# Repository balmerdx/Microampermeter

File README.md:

# Микроамперметр

Микроамперметр перфекциониста, с возможностью посмотреть график и гистограмму получаемого тока.
Предназначен для того, что-бы отлаживать низкопотребляющие железки,
которые во сне потребляют микроамперы, а когда проснулись, то могут потреблять десятки миллиампер.

* [Видео с возможностями прибора.](https://www.youtube.com/watch?v=IdX-KkagfNQ)

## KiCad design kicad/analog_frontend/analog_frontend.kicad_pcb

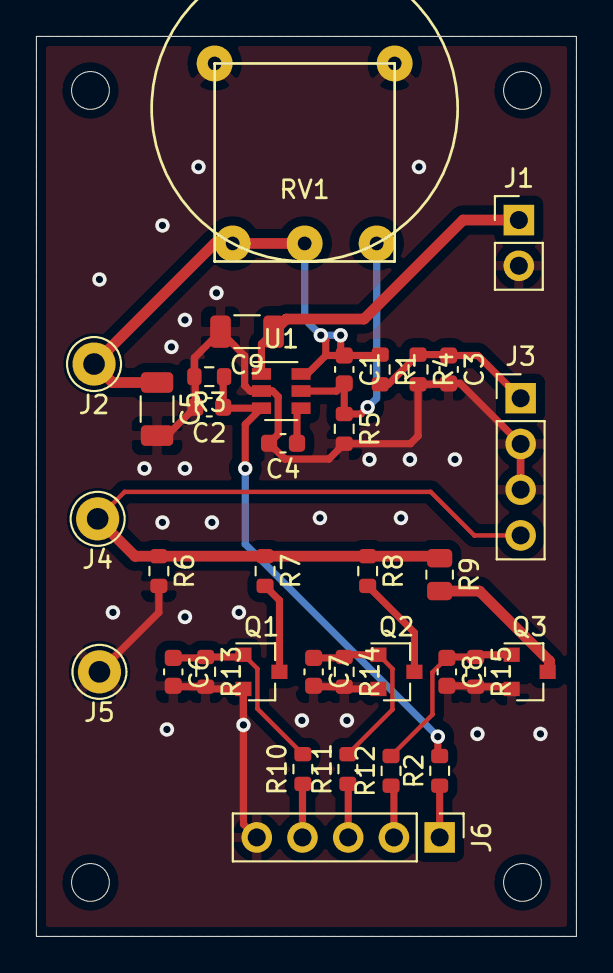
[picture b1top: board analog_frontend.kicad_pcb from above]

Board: 2 copper layers, 30.0 x 50.0 mm, 35 parts (0 on the bottom side), 18 nets.

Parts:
C1: 22; C_0603_1608Metric
C2, C6, C7, C8: 22n; C_0603_1608Metric
C3: 1n; C_0603_1608Metric
C4: 10n; C_0603_1608Metric
C5: 25u; C_1206_3216Metric
C9: 10u; C_1206_3216Metric
J1: Power; PinHeader_1x02_P2.54mm_Vertical
J2: Vout; Pin_D1.0mm_L10.0mm_LooseFit
J3: ADC; PinHeader_1x04_P2.54mm_Vertical
J4: Isense; Pin_D1.0mm_L10.0mm_LooseFit
J5: GND; Pin_D1.0mm_L10.0mm_LooseFit
J6: Digital; PinHeader_1x05_P2.54mm_Vertical
Q1, Q2: SI2302; SOT-23
Q3: IRLML2502; SOT-23
R1, R4: 2k; R_0603_1608Metric
R2, R5: 10k; R_0603_1608Metric
R3: 330k; R_0603_1608Metric
R6: 1k; R_0603_1608Metric
R7: 100; R_0603_1608Metric
R8: 10; R_0603_1608Metric
R9: 1; R_0805_2012Metric
R10, R11, R12: 4.7k; R_0603_1608Metric
R13, R14, R15: 68k; R_0603_1608Metric
RV1: 20k; Potentiometer_10mm
U1: TPS79301-EP; SOT-23-6

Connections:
+BATT: C9.1, J1.1, U1.1
/Vout: C1.1, C5.1, J2.1, R1.1, RV1.1, RV1.2, U1.6
EN_V: J6.1, R2.1
GND: C2.2, C3.2, C4.2, C5.2, C6.2, C7.2, C8.2, C9.2, J1.2, J3.2, J3.3, J5.1, J6.5, Q1.2, Q2.2, Q3.2, R3.2, R4.2, R5.2, R6.2, R13.2, R14.2, R15.2, RV1.4, RV1.5, U1.2
I_ADC: J3.4, J4.1, R6.1, R7.1, R8.1, R9.1
unnamed: C1.2, R5.1, RV1.3, U1.5
unnamed: C2.1, R2.2, R3.1, U1.3
unnamed: C4.1, U1.4
unnamed: C6.1, Q1.1, R10.2, R13.1
unnamed: C7.1, Q2.1, R11.2, R14.1
unnamed: C8.1, Q3.1, R12.2, R15.1
unnamed: Q1.3, R7.2
unnamed: Q2.3, R8.2
unnamed: Q3.3, R9.2
ON_1: J6.2, R12.1
ON_10: J6.3, R11.1
ON_100: J6.4, R10.1
V_ADC: C3.1, J3.1, R1.2, R4.1

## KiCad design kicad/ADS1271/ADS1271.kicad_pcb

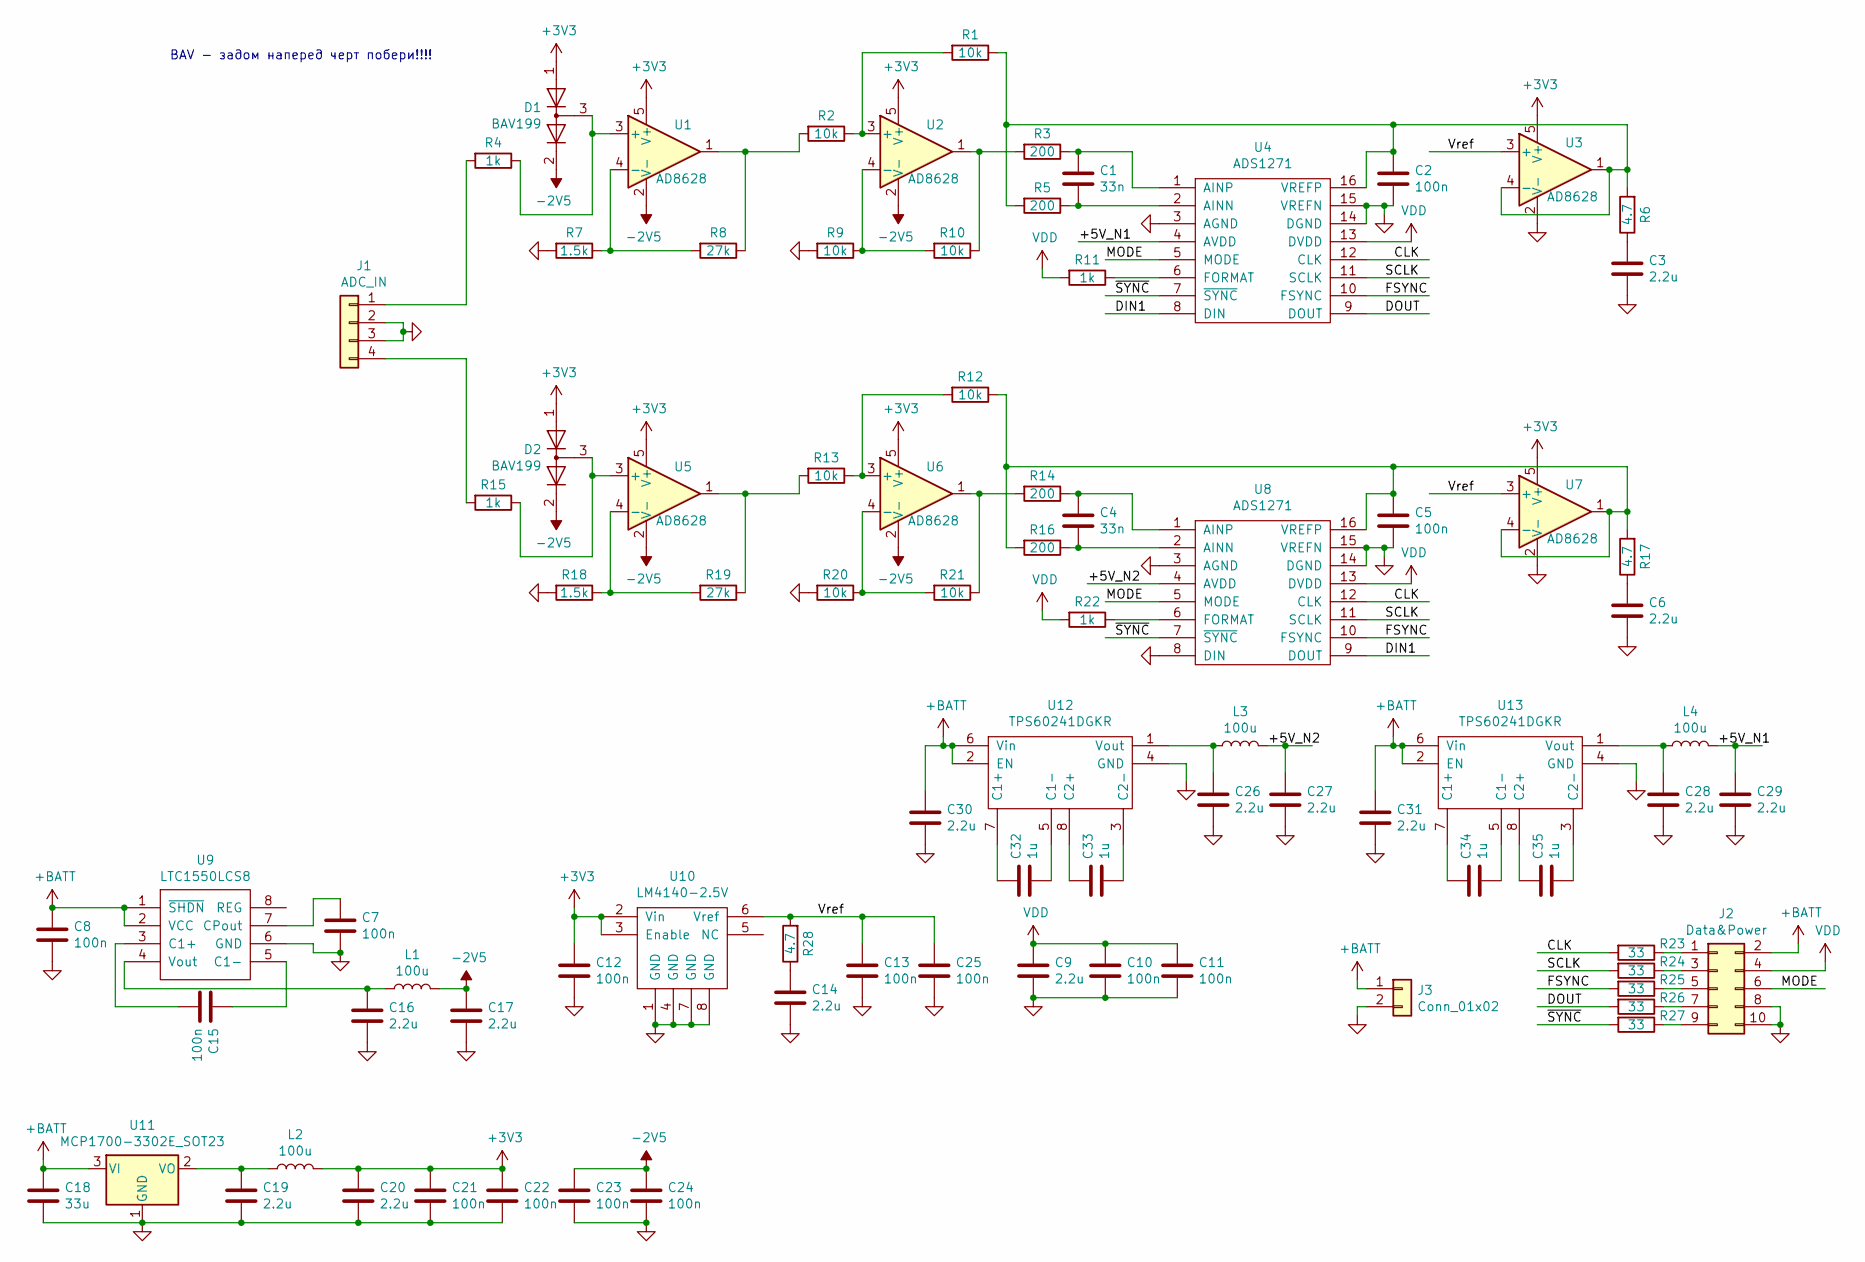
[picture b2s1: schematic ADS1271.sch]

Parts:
C1, C4: 33n; C_Disc_D7.5mm_W2.5mm_P5.00mm
C2, C5, C7, C8, C10, C11, C12, C13, C15, C21, C22, C23, C24, C25: 100n; C_0603_1608Metric
C3, C6, C9, C14, C16, C17, C19, C20, C26, C27, C28, C29, C30, C31: 2.2u; C_0805_2012Metric
C18: 33u; C_1206_3216Metric
C32, C33, C34, C35: 1u; C_0603_1608Metric
D1, D2: BAV199; SOT-23
J1: ADC_IN; PinHeader_1x04_P2.54mm_Vertical
J2: Data&Power; PinHeader_2x05_P2.54mm_Horizontal
J3: Conn_01x02; PinHeader_1x02_P2.54mm_Vertical
L1, L2, L3, L4: 100u; L_Axial_L9.5mm_D4.0mm_P12.70mm_Horizontal_Fastron_SMCC
R1, R2, R9, R10, R12, R13, R20, R21: 10k; R_0603_1608Metric
R3, R5, R14, R16: 200; R_0603_1608Metric
R4, R11, R15, R22: 1k; R_0603_1608Metric
R6, R17, R28: 4.7; R_0603_1608Metric
R7, R18: 1.5k; R_0603_1608Metric
R8, R19: 27k; R_0603_1608Metric
R23, R24, R25, R26, R27: 33; R_0603_1608Metric
U1, U2, U3, U5, U6, U7: AD8628; SOT-23-5
U4, U8: ADS1271; TSSOP-16_4.4x5mm_P0.65mm
U9: LTC1550LCS8; TSSOP-8_3x3mm_P0.65mm
U10: LM4140-2.5V; SO-8_3.9x4.9mm_P1.27mm
U11: MCP1700-3302E_SOT23; SOT-23
U12, U13: TPS60241DGKR; TSSOP-8_3x3mm_P0.65mm

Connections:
+3V3: C12.1, C20.1, C21.1, C22.1, D1.1 (K), D2.1 (K), L2.2, U1.5 (V+), U2.5 (V+), U3.5 (V+), U5.5 (V+), U6.5 (V+), U7.5 (V+), U10.2 (Vin), U10.3 (Enable)
+BATT: C8.1, C18.1, C30.1, C31.1, J2.2, J3.1, U9.1 (~SHDN), U9.2 (VCC), U11.3 (VI), U12.2 (EN), U12.6 (Vin), U13.2 (EN), U13.6 (Vin)
-2V5: C17.1, C23.1, C24.1, D1.2 (A), D2.2 (A), L1.2, U1.2 (V-), U2.2 (V-), U5.2 (V-), U6.2 (V-)
/+5V_N1: C29.1, L4.2, U4.4 (AVDD)
/+5V_N2: C27.1, L3.2, U8.4 (AVDD)
/CLK: R23.2, U4.12 (CLK), U8.12 (CLK)
/DIN1: U4.8 (DIN), U8.9 (DOUT)
/DOUT: R26.2, U4.9 (DOUT)
/FSYNC: R25.2, U4.10 (FSYNC), U8.10 (FSYNC)
/MODE: J2.6, U4.5 (MODE), U8.5 (MODE)
/SCLK: R24.2, U4.11 (SCLK), U8.11 (SCLK)
/Vref: C13.1, C25.1, R28.2, U3.3 (+), U7.3 (+), U10.6 (Vref)
/~SYNC: R27.2, U4.7 (~SYNC), U8.7 (~SYNC)
GND: C2.2, C3.2, C5.2, C6.2, C7.2, C8.2, C9.2, C10.2, C11.2, C12.2, C13.2, C14.2, C16.2, C17.2, C18.2, C19.2, C20.2, C21.2, C22.2, C23.2, C24.2, C25.2, C26.2, C27.2, C28.2, C29.2, C30.2, C31.2, J1.2, J1.3, J2.8, J2.10, J3.2, R7.2, R9.2, R18.2, R20.2, U3.2 (V-), U4.3 (AGND), U4.14 (DGND), U4.15 (VREFN), U7.2 (V-), U8.3 (AGND), U8.8 (DIN), U8.14 (DGND), U8.15 (VREFN), U9.6 (GND), U10.1 (GND), U10.4 (GND), U10.7 (GND), U10.8 (GND), U11.1 (GND), U12.4 (GND), U13.4 (GND)
unnamed: C1.1, R3.1, U4.1 (AINP)
unnamed: C1.2, R5.1, U4.2 (AINN)
unnamed: C2.1, R1.1, R5.2, R6.2, U3.1, U3.4 (-), U4.16 (VREFP)
unnamed: C3.1, R6.1
unnamed: C4.1, R14.1, U8.1 (AINP)
unnamed: C4.2, R16.1, U8.2 (AINN)
unnamed: C5.1, R12.1, R16.2, R17.2, U7.1, U7.4 (-), U8.16 (VREFP)
unnamed: C6.1, R17.1
unnamed: C7.1, U9.7 (CPout)
unnamed: C14.1, R28.1
unnamed: C15.1, U9.5 (C1-)
unnamed: C15.2, U9.3 (C1+)
unnamed: C16.1, L1.1, U9.4 (Vout)
unnamed: C19.1, L2.1, U11.2 (VO)
unnamed: C26.1, L3.1, U12.1 (Vout)
unnamed: C28.1, L4.1, U13.1 (Vout)
unnamed: C32.1, U12.7 (C1+)
unnamed: C32.2, U12.5 (C1-)
unnamed: C33.1, U12.8 (C2+)
unnamed: C33.2, U12.3 (C2-)
unnamed: C34.1, U13.7 (C1+)
unnamed: C34.2, U13.5 (C1-)
unnamed: C35.1, U13.8 (C2+)
unnamed: C35.2, U13.3 (C2-)
unnamed: D1.3 (K), R4.1, U1.3 (+)
unnamed: D2.3 (K), R15.1, U5.3 (+)
unnamed: J1.1, R4.2
unnamed: J1.4, R15.2
unnamed: J2.1, R23.1
unnamed: J2.3, R24.1
unnamed: J2.5, R25.1
unnamed: J2.7, R26.1
unnamed: J2.9, R27.1
unnamed: R1.2, R2.1, U2.3 (+)
unnamed: R2.2, R8.1, U1.1
unnamed: R7.1, R8.2, U1.4 (-)
unnamed: R3.2, R10.1, U2.1
unnamed: R9.1, R10.2, U2.4 (-)
unnamed: R11.1, U4.6 (FORMAT)
unnamed: R12.2, R13.1, U6.3 (+)
unnamed: R13.2, R19.1, U5.1
unnamed: R14.2, R21.1, U6.1
unnamed: R18.1, R19.2, U5.4 (-)
unnamed: R20.1, R21.2, U6.4 (-)
unnamed: R22.1, U8.6 (FORMAT)
VDD: C9.1, C10.1, C11.1, J2.4, R11.2, R22.2, U4.13 (DVDD), U8.13 (DVDD)

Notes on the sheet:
BAV - задом наперед черт побери!!!!

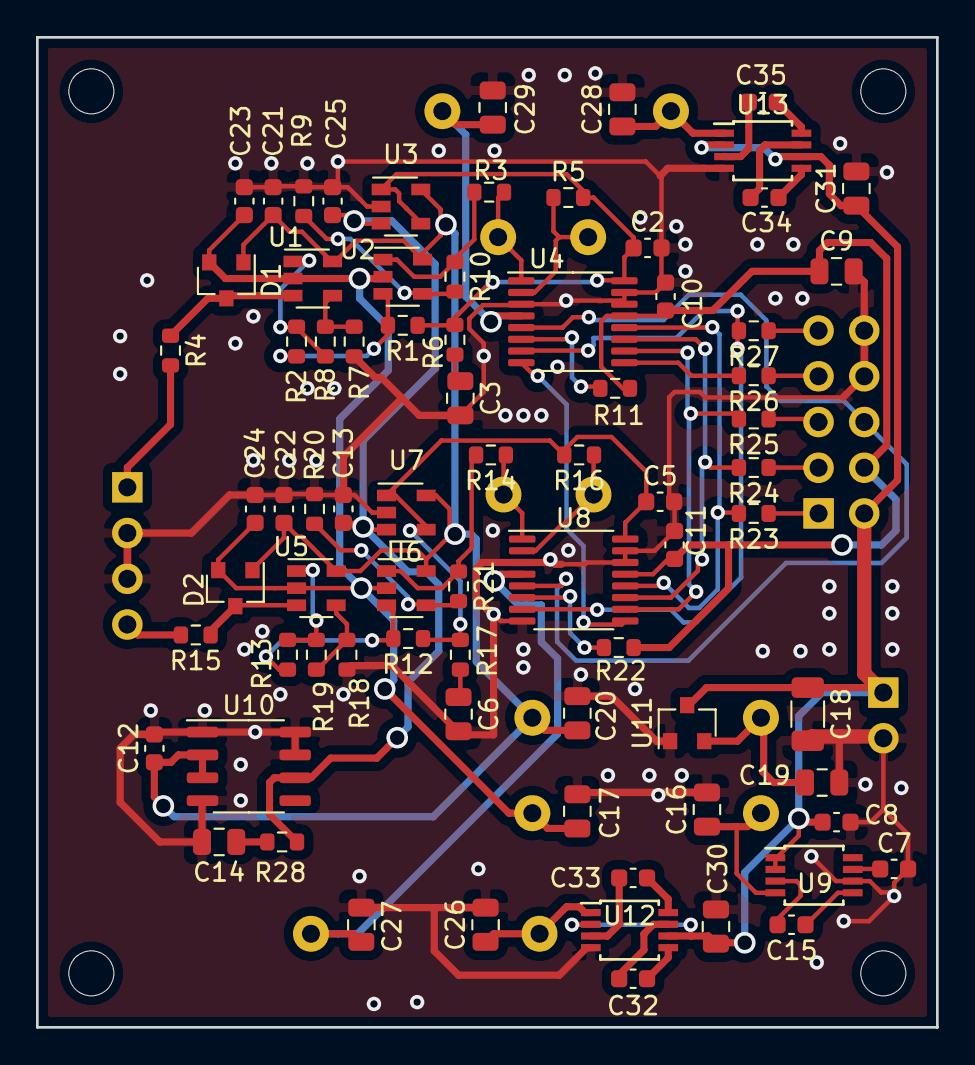
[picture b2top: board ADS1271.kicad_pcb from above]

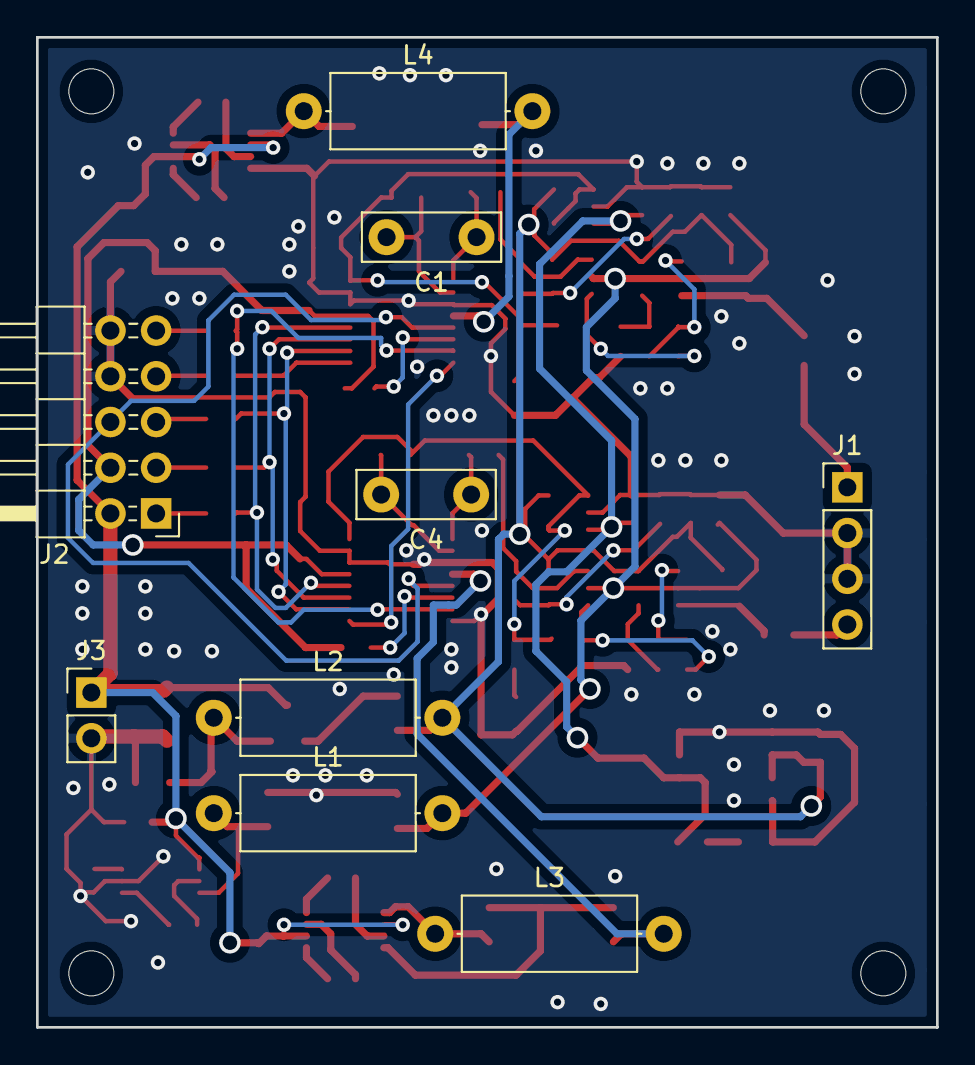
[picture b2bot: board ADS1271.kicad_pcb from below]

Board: 2 copper layers, 50.0 x 55.0 mm, 85 parts (9 on the bottom side), 60 nets.

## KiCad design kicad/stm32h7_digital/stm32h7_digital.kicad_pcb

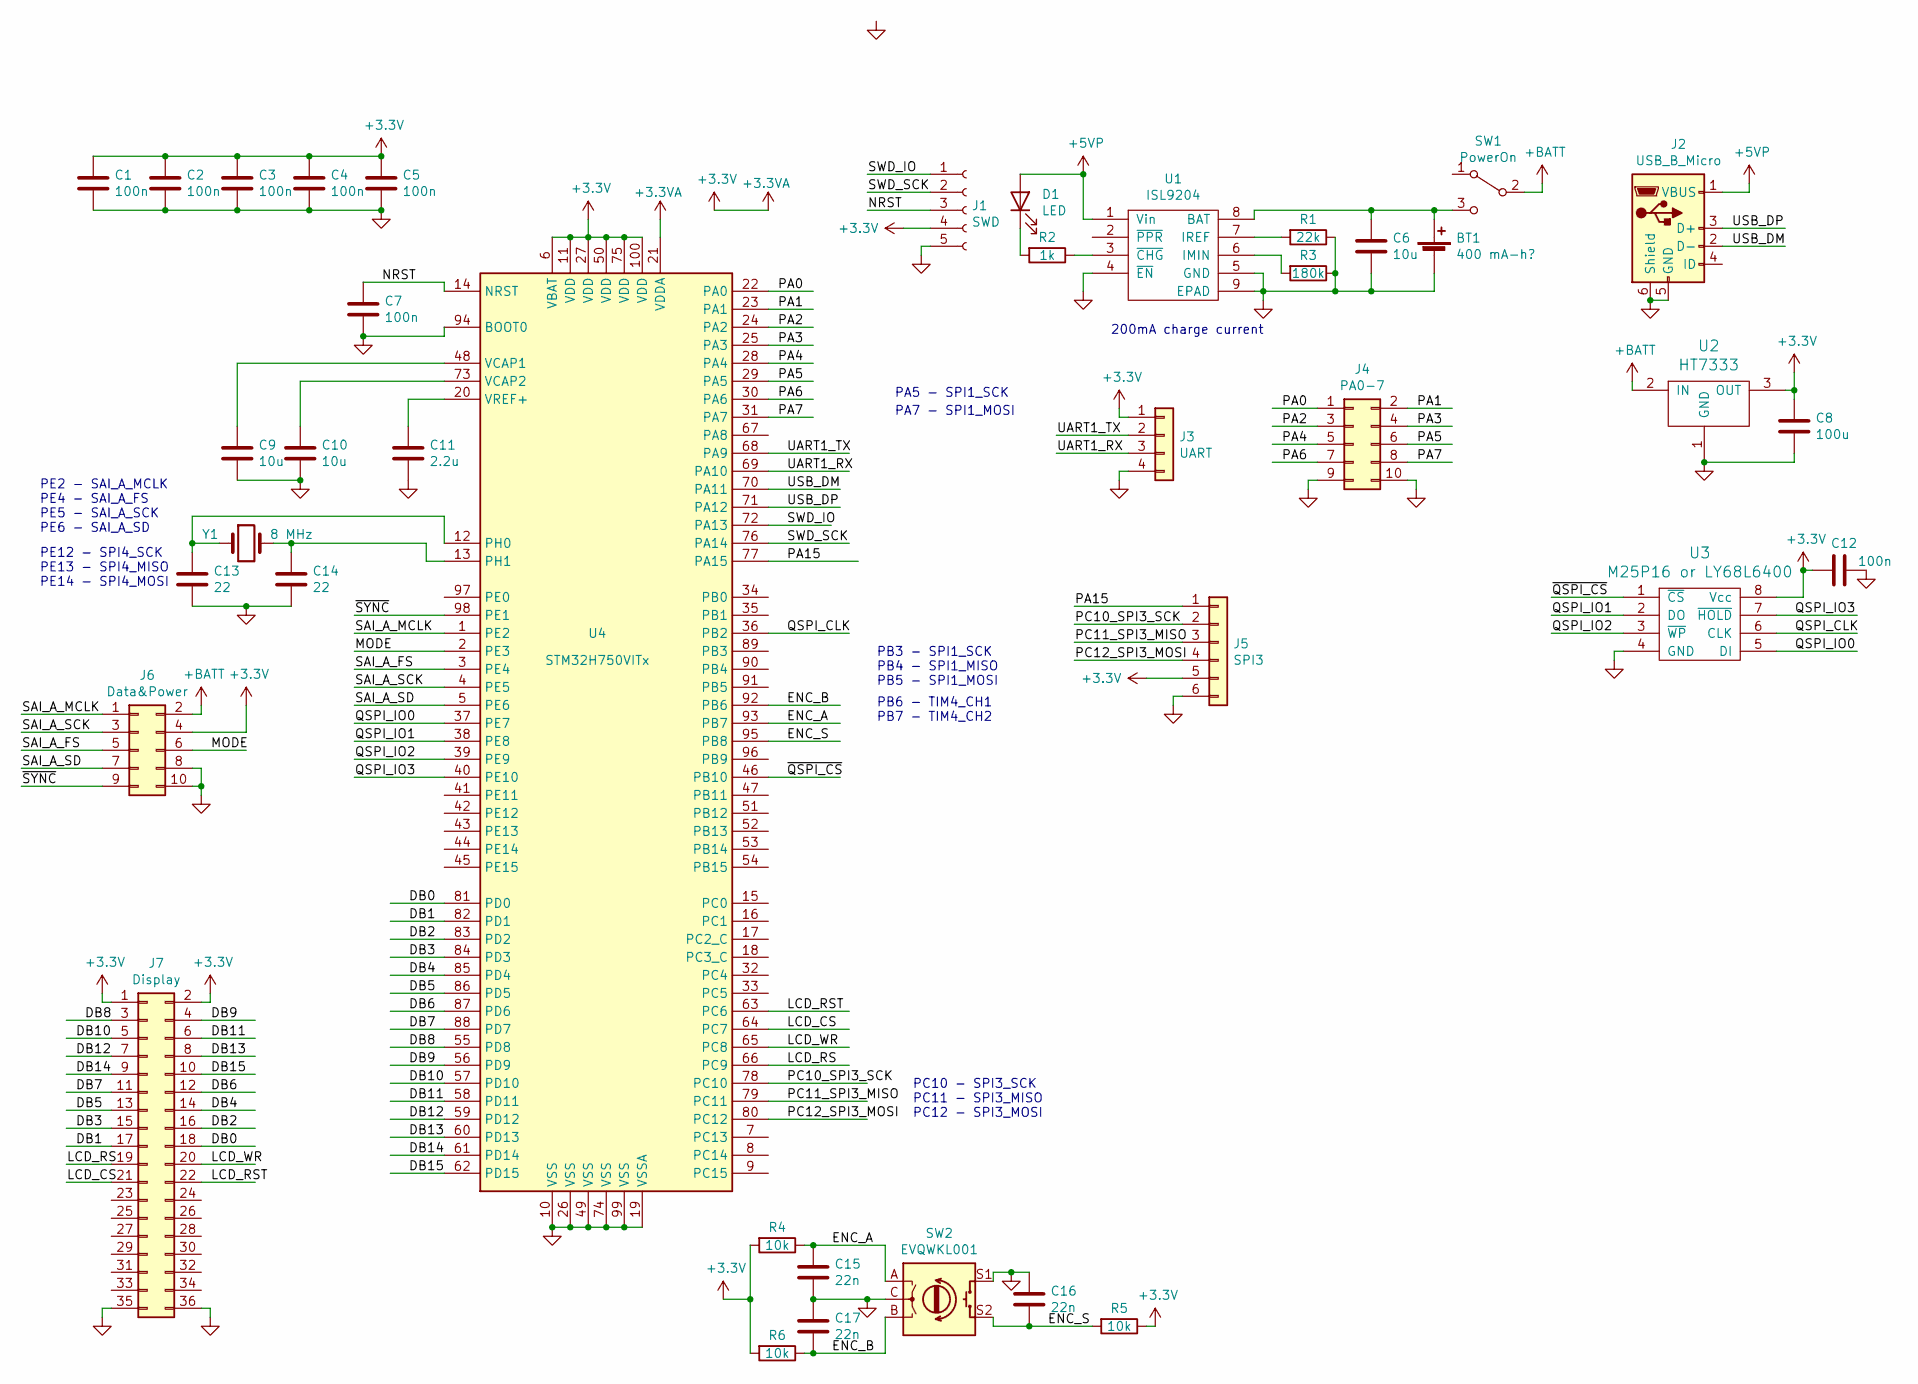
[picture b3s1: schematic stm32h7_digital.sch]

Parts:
BT1: 400 mA-h?; PinSocket_1x02_P2.54mm_Vertical
C1, C2, C3, C4, C5, C7, C12: 100n; C_0603_1608Metric
C6, C9, C10: 10u; C_1206_3216Metric
C8: 100u; C_1206_3216Metric
C11: 2.2u; C_0805_2012Metric
C13, C14: 22; C_0603_1608Metric
C15, C16, C17: 22n; C_0603_1608Metric
D1: LED; LED_0805_2012Metric_Pad1.15x1.40mm_HandSolder
J1: SWD; PinSocket_1x05_P1.27mm_Vertical
J2: USB_B_Micro; USB_Micro-B_Molex-105017-0001
J3: UART; PinHeader_1x04_P2.54mm_Horizontal
J4: PA0-7; PinSocket_2x05_P2.54mm_Horizontal
J5: SPI3; PinSocket_1x06_P1.27mm_Vertical
J6: Data&Power; PinSocket_2x05_P2.54mm_Horizontal
J7: Display; PinHeader_2x18_P2.54mm_Vertical
R1: 22k; R_0603_1608Metric
R2: 1k; R_0603_1608Metric
R3: 180k; R_0603_1608Metric
R4, R5, R6: 10k; R_0603_1608Metric
SW1: PowerOn; SW_Angled_with_GND
SW2: EVQWKL001; Encoder_EVQWK4
U1: ISL9204; DFN-8-1EP_3x2mm_P0.5mm_EP1.75x1.65mm
U2: HT7333; SOT-89-3
U3: M25P16 or LY68L6400; SOIC-8_3.9x4.9mm_P1.27mm
U4: STM32H750VITx; LQFP-100_14x14mm_P0.5mm
Y1: 8 MHz; Crystal_SMD_5032-2Pin_5.0x3.2mm

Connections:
+3.3VA: C1.1, C2.1, C3.1, C4.1, C5.1, C8.1, C12.2, J1.4, J3.1, J5.5, J6.4, J7.1, J7.2, R4.2, R5.1, R6.2, U2.3 (OUT), U3.8 (Vcc), U4.6 (VBAT), U4.11 (VDD), U4.21 (VDDA), U4.27 (VDD), U4.50 (VDD), U4.75 (VDD), U4.100 (VDD)
+5VP: D1.2 (A), J2.1 (VBUS), U1.1 (Vin)
+BATT: J6.2, SW1.2 (B), U2.2 (IN)
/DB0: J7.18, U4.81 (PD0)
/DB1: J7.17, U4.82 (PD1)
/DB2: J7.16, U4.83 (PD2)
/DB3: J7.15, U4.84 (PD3)
/DB4: J7.14, U4.85 (PD4)
/DB5: J7.13, U4.86 (PD5)
/DB6: J7.12, U4.87 (PD6)
/DB7: J7.11, U4.88 (PD7)
/DB8: J7.3, U4.55 (PD8)
/DB9: J7.4, U4.56 (PD9)
/DB10: J7.5, U4.57 (PD10)
/DB11: J7.6, U4.58 (PD11)
/DB12: J7.7, U4.59 (PD12)
/DB13: J7.8, U4.60 (PD13)
/DB14: J7.9, U4.61 (PD14)
/DB15: J7.10, U4.62 (PD15)
/ENC_A: C15.1, R4.1, SW2.A, U4.93 (PB7)
/ENC_B: C17.2, R6.1, SW2.B, U4.92 (PB6)
/ENC_S: C16.2, R5.2, SW2.S2, U4.95 (PB8)
/LCD_CS: J7.21, U4.64 (PC7)
/LCD_RS: J7.19, U4.66 (PC9)
/LCD_RST: J7.22, U4.63 (PC6)
/LCD_WR: J7.20, U4.65 (PC8)
/MODE: J6.6, U4.2 (PE3)
/NRST: C7.1, J1.3, U4.14 (NRST)
/PA0: J4.1, U4.22 (PA0)
/PA1: J4.2, U4.23 (PA1)
/PA2: J4.3, U4.24 (PA2)
/PA3: J4.4, U4.25 (PA3)
/PA4: J4.5, U4.28 (PA4)
/PA5: J4.6, U4.29 (PA5)
/PA6: J4.7, U4.30 (PA6)
/PA7: J4.8, U4.31 (PA7)
/PA15: J5.1, U4.77 (PA15)
/PC10_SPI3_SCK: J5.2, U4.78 (PC10)
/PC11_SPI3_MISO: J5.3, U4.79 (PC11)
/PC12_SPI3_MOSI: J5.4, U4.80 (PC12)
/QSPI_CLK: U3.6 (CLK), U4.36 (PB2)
/QSPI_IO0: U3.5 (DI), U4.37 (PE7)
/QSPI_IO1: U3.2 (DO), U4.38 (PE8)
/QSPI_IO2: U3.3 (~WP), U4.39 (PE9)
/QSPI_IO3: U3.7 (~HOLD), U4.40 (PE10)
/SAI_A_FS: J6.5, U4.3 (PE4)
/SAI_A_MCLK: J6.1, U4.1 (PE2)
/SAI_A_SCK: J6.3, U4.4 (PE5)
/SAI_A_SD: J6.7, U4.5 (PE6)
/SWD_IO: J1.1, U4.72 (PA13)
/SWD_SCK: J1.2, U4.76 (PA14)
/UART1_RX: J3.3, U4.69 (PA10)
/UART1_TX: J3.2, U4.68 (PA9)
/USB_DM: J2.2 (D-), U4.70 (PA11)
/USB_DP: J2.3 (D+), U4.71 (PA12)
/~QSPI_CS: U3.1 (~CS), U4.46 (PB10)
/~SYNC: J6.9, U4.98 (PE1)
GND: BT1.2 (-), C1.2, C2.2, C3.2, C4.2, C5.2, C6.2, C7.2, C8.2, C9.2, C10.2, C11.2, C12.1, C13.2, C14.2, C15.2, C16.1, C17.1, J1.5, J2.5 (GND), J2.6 (Shield), J3.4, J4.9, J4.10, J5.6, J6.8, J6.10, J7.35, J7.36, R1.1, R3.1, SW2.C, SW2.GND, SW2.PAD, SW2.S1, U1.4 (~EN), U1.5 (GND), U1.9 (EPAD), U2.1 (GND), U3.4 (GND), U4.10 (VSS), U4.19 (VSSA), U4.26 (VSS), U4.49 (VSS), U4.74 (VSS), U4.94 (BOOT0), U4.99 (VSS)
unnamed: BT1.1 (+), C6.1, SW1.3 (C), U1.8 (BAT)
unnamed: C9.1, U4.48 (VCAP1)
unnamed: C10.1, U4.73 (VCAP2)
unnamed: C11.1, U4.20 (VREF+)
unnamed: C13.1, U4.12 (PH0), Y1.1
unnamed: C14.1, U4.13 (PH1), Y1.2
unnamed: D1.1 (K), R2.2
unnamed: R1.2, U1.7 (IREF)
unnamed: R2.1, U1.3 (~CHG)
unnamed: R3.2, U1.6 (IMIN)

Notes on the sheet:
200mA charge current
PB3 - SPI1_SCK PB4 - SPI1_MISO PB5 - SPI1_MOSI
PC10 - SPI3_SCK PC11 - SPI3_MISO PC12 - SPI3_MOSI
PB6 - TIM4_CH1 PB7 - TIM4_CH2
PA5 - SPI1_SCK
PA7 - SPI1_MOSI
PE12 - SPI4_SCK PE13 - SPI4_MISO PE14 - SPI4_MOSI
PE2 - SAI_A_MCLK PE4 - SAI_A_FS PE5 - SAI_A_SCK PE6 - SAI_A_SD

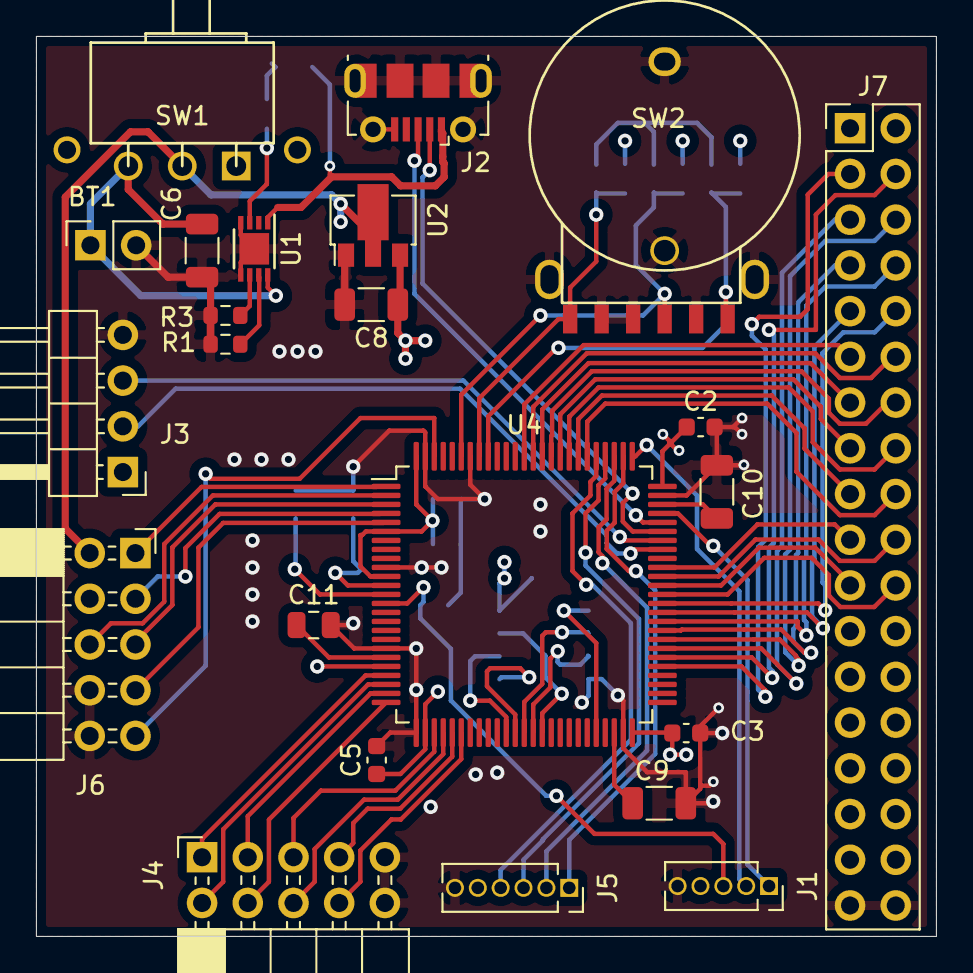
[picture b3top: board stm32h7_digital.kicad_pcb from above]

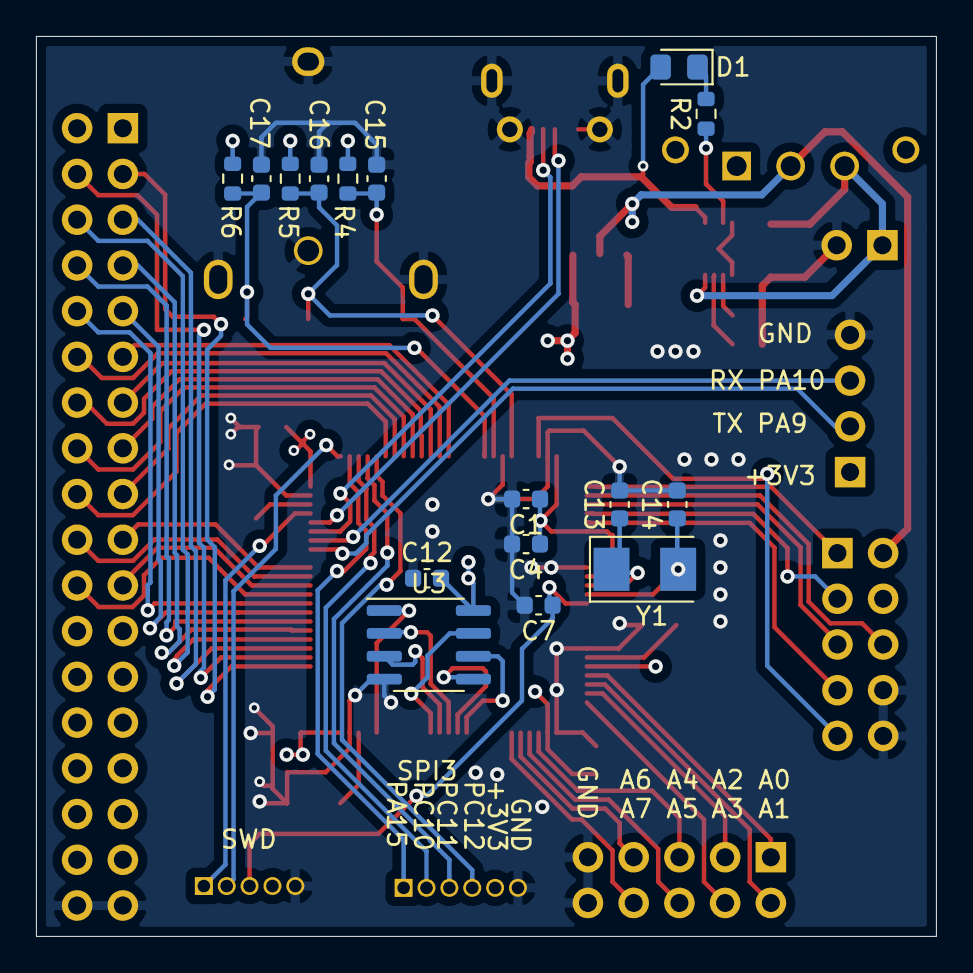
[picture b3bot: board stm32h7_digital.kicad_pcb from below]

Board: 4 copper layers, 50.0 x 50.0 mm, 39 parts (16 on the bottom side), 68 nets.

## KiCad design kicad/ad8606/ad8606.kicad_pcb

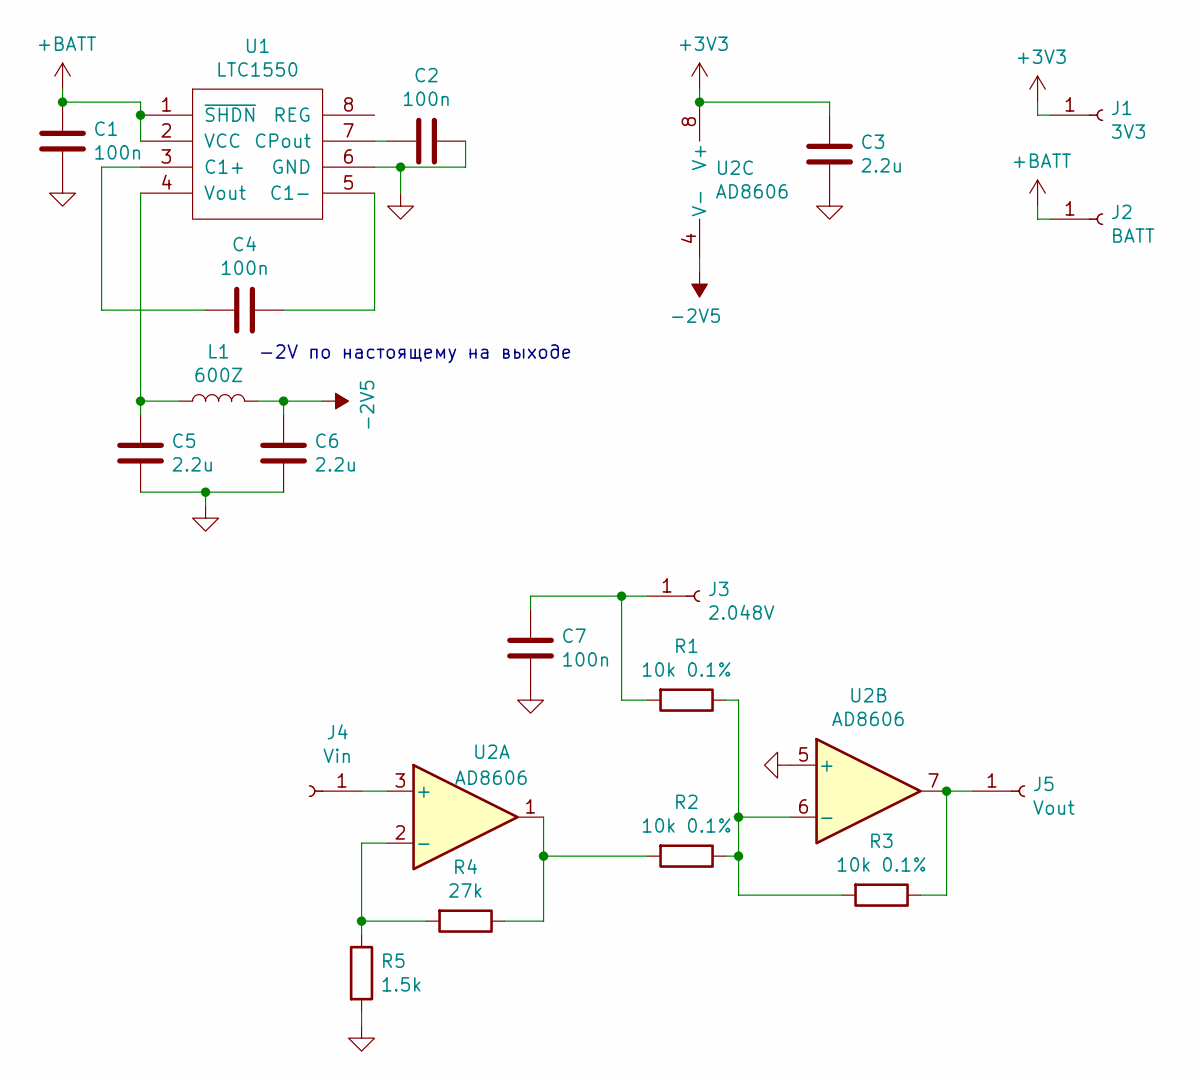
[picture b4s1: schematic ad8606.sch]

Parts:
C1, C2, C4, C7: 100n; C_0603_1608Metric
C3, C5, C6: 2.2u; C_0805_2012Metric
J1: 3V3; TestPoint_Pad_1.5x1.5mm
J2: BATT; TestPoint_Pad_1.5x1.5mm
J3: 2.048V; TestPoint_Pad_1.5x1.5mm
J4: Vin; TestPoint_Pad_1.5x1.5mm
J5: Vout; TestPoint_Pad_1.5x1.5mm
L1: 600Z; L_1206_3216Metric
R1, R2, R3: 10k 0.1%; R_0603_1608Metric
R4: 27k; R_0603_1608Metric
R5: 1.5k; R_0603_1608Metric
U1: LTC1550; TSSOP-8_3x3mm_P0.65mm
U2: AD8606; TSSOP-8_3x3mm_P0.65mm

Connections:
+3V3: C3.1, J1.1, U2.8 (V+)
+BATT: C1.2, J2.1, U1.1 (~SHDN), U1.2 (VCC)
-2V5: C6.1, L1.2, U2.4 (V-)
GND: C1.1, C2.1, C3.2, C5.2, C6.2, C7.1, R5.2, U1.6 (GND), U2.5 (+)
unnamed: C2.2, U1.7 (CPout)
unnamed: C4.1, U1.5 (C1-)
unnamed: C4.2, U1.3 (C1+)
unnamed: C5.1, L1.1, U1.4 (Vout)
unnamed: C7.2, J3.1, R1.2
unnamed: J4.1, U2.3 (+)
unnamed: J5.1, R3.1, U2.7
unnamed: R1.1, R2.1, R3.2, U2.6 (-)
unnamed: R2.2, R4.1, U2.1
unnamed: R4.2, R5.1, U2.2 (-)

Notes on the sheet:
-2V по настоящему на выходе

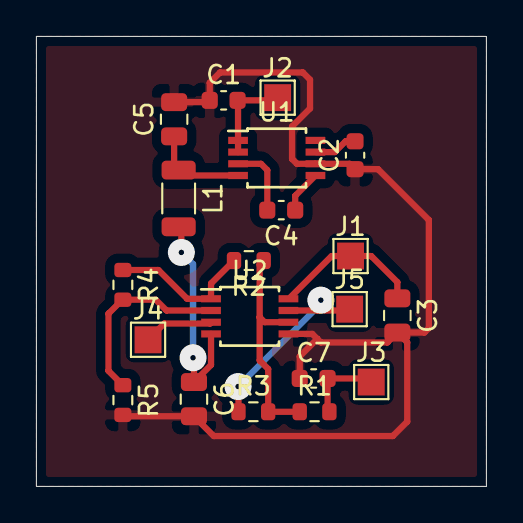
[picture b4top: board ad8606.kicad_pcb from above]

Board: 2 copper layers, 25.0 x 25.0 mm, 20 parts (0 on the bottom side), 14 nets.

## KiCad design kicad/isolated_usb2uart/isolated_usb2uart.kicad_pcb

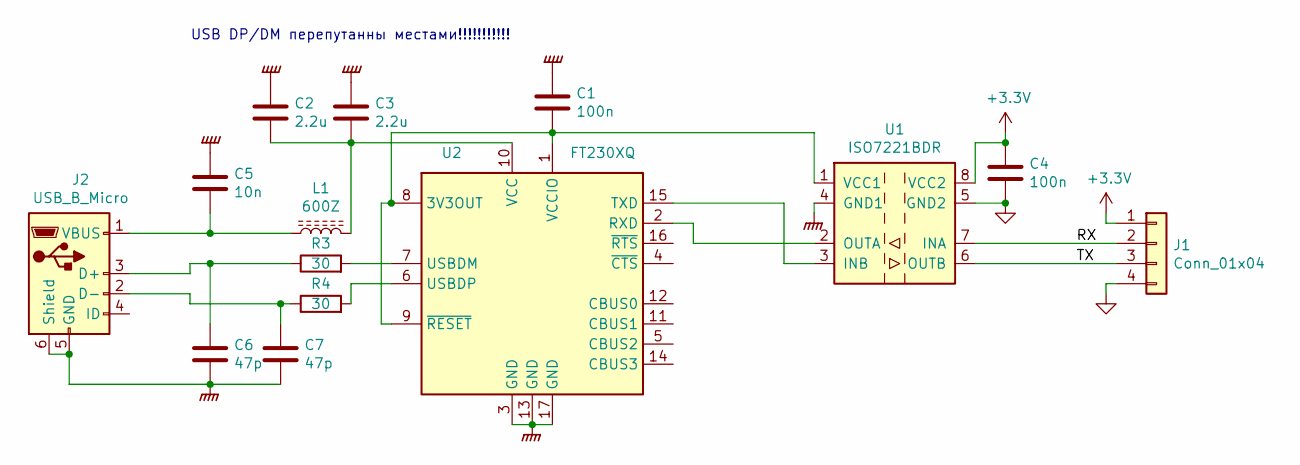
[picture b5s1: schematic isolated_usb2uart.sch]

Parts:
C1, C4: 100n; C_0603_1608Metric
C2, C3: 2.2u; C_0805_2012Metric
C5: 10n; C_0603_1608Metric
C6, C7: 47p; C_0603_1608Metric
J1: Conn_01x04; PinHeader_1x04_P2.54mm_Horizontal
J2: USB_B_Micro; USB_Micro-B_Molex-105017-0001
L1: 600Z; R_1206_3216Metric
R3, R4: 30; R_0603_1608Metric
U1: ISO7221BDR; SOIC-8_3.9x4.9mm_P1.27mm
U2: FT230XQ; QFN-16-1EP_4x4mm_P0.65mm_EP2.1x2.1mm

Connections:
+3V3: C4.1, J1.1, U1.8 (VCC2)
/RX: J1.2, U1.7 (INA)
/TX: J1.3, U1.6 (OUTB)
GND: C4.2, J1.4, U1.5 (GND2)
GNDPWR: C1.1, C2.1, C3.1, C5.1, C6.2, C7.2, J2.5 (GND), J2.6 (Shield), U1.4 (GND1), U2.3 (GND), U2.13 (GND), U2.17 (GND)
unnamed: C1.2, U1.1 (VCC1), U2.1 (VCCIO), U2.8 (3V3OUT), U2.9 (~RESET)
unnamed: C2.2, C3.2, L1.2, U2.10 (VCC)
unnamed: C5.2, J2.1 (VBUS), L1.1
unnamed: C6.1, J2.3 (D+), R3.1
unnamed: C7.1, J2.2 (D-), R4.1
unnamed: R3.2, U2.7 (USBDM)
unnamed: R4.2, U2.6 (USBDP)
unnamed: U1.2 (OUTA), U2.2 (RXD)
unnamed: U1.3 (INB), U2.15 (TXD)

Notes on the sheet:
USB DP/DM перепутанны местами!!!!!!!!!!!

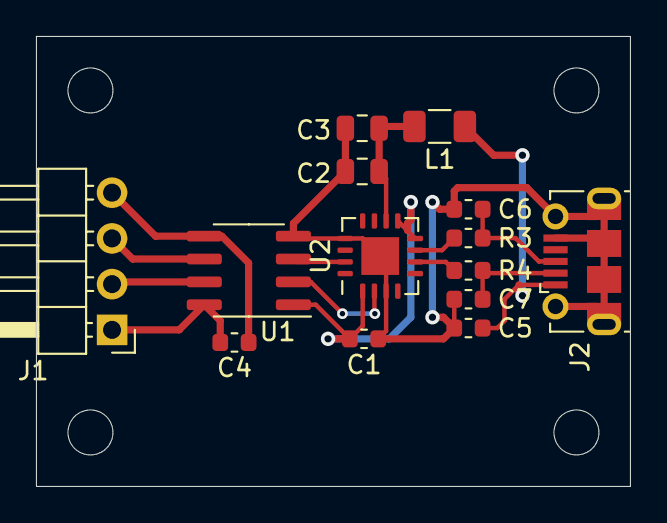
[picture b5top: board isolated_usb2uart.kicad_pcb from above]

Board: 2 copper layers, 33.0 x 25.0 mm, 14 parts (0 on the bottom side), 14 nets.

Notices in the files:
h7code/Core/Src/stm32h7xx_hal_msp.c:
© Copyright (c) 2020 STMicroelectronics.
All rights reserved.
This software component is licensed by ST under BSD 3-Clause license,
the "License"; You may not use this file except in compliance with the
License. You may obtain a copy of the License at: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
(C) COPYRIGHT STMicroelectronics *****END OF FILE
